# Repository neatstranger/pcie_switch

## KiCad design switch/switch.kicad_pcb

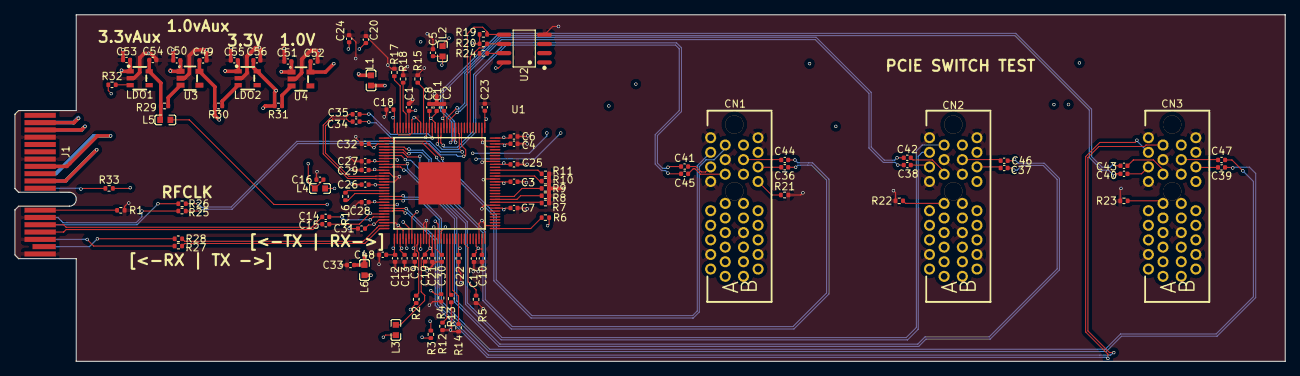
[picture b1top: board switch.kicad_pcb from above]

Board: 6 copper layers, 174.1 x 47.5 mm, 105 parts (0 on the bottom side), 93 nets.

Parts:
C1, C2, C3, C4, C5, C6, C7, C8, C9, C10, C11, C12, C13, C14, C15, C16, C17, C19, C20, C21, C22, C23, C24, C26, C27, C28, C29, C30, C31, C32, C34, C35, C36, C37, C38, C39, C40, C41, C42, C43, C44, C45, C46, C47, C48: 100n; C_0402_1005Metric
C18, C25, C33: 10u; C_0402_1005Metric
C49, C50, C51, C52, C53, C55: 1u; C_0402_1005Metric
C54, C56: 2.2u; C_0402_1005Metric
CN1, CN2, CN3: 3183-10110P1T; CONN-TH_36P-P1.00-V_3183-XXXXXPXT
J1: Bus_PCI_Express_x1; BUS_PCIexpress_x1
L1, L2, L3, L4, L5, L6: MPZ1608D101BTA00; L0603
LDO1, LDO2: TPS70933DBVR; SOT-23-5_L3.0-W1.7-P0.95-LS2.8-BR
R1, R4, R5, R6, R10, R11, R17, R18, R21, R22, R23: 330; R_0402_1005Metric
R2, R3, R19, R20: 5.1k; R_0402_1005Metric
R7, R8, R9, R24: 10k; R_0402_1005Metric
R12, R13, R14: 1k; R_0402_1005Metric
R15: 475; R_0402_1005Metric
R16: 1.42k; R_0402_1005Metric
R25, R26, R27, R28, R29, R30, R31, R32, R33: 0; R_0402_1005Metric
U1: PI7C9X2G404SLBFDEX; LQFP-128_L14.0-W14.0-P0.40-LS16.0-BL-EP5.8
U2: M24C04-WMN6TP; SOIC-8_L4.9-W3.9-P1.27-LS6.0-BL
U3, U4: TLV73310PDBVR; TSOT-23-5_L2.9-W1.6-P0.95-LS2.8-BR

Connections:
/3.3V_PCIE: C50.1, C51.1, C53.2, C55.2, CN1.A5 (TCK), CN1.A6 (TDI), CN1.A8 (TMS), CN1.A9 (+3.3V), CN1.A10 (+3.3V), CN1.B8 (+3.3V), CN1.B9 (nTRST), CN1.B10 (+3.3VAux), CN2.A5 (TCK), CN2.A6 (TDI), CN2.A8 (TMS), CN2.A9 (+3.3V), CN2.A10 (+3.3V), CN2.B8 (+3.3V), CN2.B9 (nTRST), CN2.B10 (+3.3VAux), CN3.A5 (TCK), CN3.A6 (TDI), CN3.A8 (TMS), CN3.A9 (+3.3V), CN3.A10 (+3.3V), CN3.B8 (+3.3V), CN3.B9 (nTRST), CN3.B10 (+3.3VAux), J1.A9 (+3.3V), J1.A10 (+3.3V), J1.B8 (+3.3V), J1.B10 (3.3Vaux), LDO1.1 (IN), LDO2.1 (IN), R32.1, U3.1 (IN), U4.1 (IN)
/+12V_PCIE: CN1.A2 (+12V), CN1.A3 (+12V), CN1.B1 (+12V), CN1.B2 (+12V), CN1.B3 (+12V), CN2.A2 (+12V), CN2.A3 (+12V), CN2.B1 (+12V), CN2.B2 (+12V), CN2.B3 (+12V), CN3.A2 (+12V), CN3.A3 (+12V), CN3.B1 (+12V), CN3.B2 (+12V), CN3.B3 (+12V), J1.A2 (+12V), J1.A3 (+12V), J1.B1 (+12V), J1.B2 (+12V), J1.B3 (+12V)
/PCIE_DOWNSTREAM1/PCIE_TX_N: C44.2, CN1.B15 (PCIE_TX_N)
/PCIE_DOWNSTREAM1/PCIE_TX_P: C36.2, CN1.B14 (PCIE_TX_P)
/PCIE_DOWNSTREAM1/REF_CLK_N: C41.2, CN1.A14 (REF_CLK_N)
/PCIE_DOWNSTREAM1/REF_CLK_P: C45.2, CN1.A13 (REF_CLK_P)
/PCIE_DOWNSTREAM2/PCIE_TX_N: C46.2, CN2.B15 (PCIE_TX_N)
/PCIE_DOWNSTREAM2/PCIE_TX_P: C37.2, CN2.B14 (PCIE_TX_P)
/PCIE_DOWNSTREAM2/REF_CLK_N: C38.2, CN2.A14 (REF_CLK_N)
/PCIE_DOWNSTREAM2/REF_CLK_P: C42.2, CN2.A13 (REF_CLK_P)
/PCIE_DOWNSTREAM3/PCIE_TX_N: C47.2, CN3.B15 (PCIE_TX_N)
/PCIE_DOWNSTREAM3/PCIE_TX_P: C39.2, CN3.B14 (PCIE_TX_P)
/PCIE_DOWNSTREAM3/REF_CLK_N: C40.2, CN3.A14 (REF_CLK_N)
/PCIE_DOWNSTREAM3/REF_CLK_P: C43.2, CN3.A13 (REF_CLK_P)
/PCIE_SWITCH/1.0Vaux: C49.1, L3.2, R30.2, U3.5 (OUT)
/PCIE_SWITCH/3.3V_PCIE: C3.1, C6.1, C9.1, C12.1, C16.1, C18.1, C48.1, L1.2, L2.2, L4.2, R2.1, R3.1, R6.1, R19.1, R20.1, U1.1 (VDDR), U1.8 (VDDR), U1.49 (VDDR), U1.64 (VDDR), U1.96 (VDDR), U2.8 (VCC)
/PCIE_SWITCH/3.3Vaux: C54.2, L5.2, LDO1.5 (OUT), R29.2
/PCIE_SWITCH/+1.0V: C1.2, C4.2, C7.2, C10.2, C13.2, C17.2, C20.2, C22.2, C23.2, C24.2, C25.2, C52.1, L6.2, U1.3 (VDDC), U1.23 (VDDC), U1.29 (VDDC), U1.31 (VDDC), U1.40 (VDDC), U1.55 (VDDC), U1.62 (VDDC), U1.65 (VDDC), U1.91 (VDDC), U4.5 (OUT)
/PCIE_SWITCH/+3.3V: C56.2, L1.1, LDO2.5 (OUT), R31.2
/PCIE_SWITCH/+AVDD: C27.1, C28.1, C29.1, C31.1, C32.1, C33.1, L6.1, U1.99 (AVDD), U1.105 (AVDD), U1.108 (AVDD), U1.119 (AVDD), U1.125 (AVDD)
/PCIE_SWITCH/+AVDDH: C26.1, L4.1, U1.113 (AVDDH)
/PCIE_SWITCH/+CVDDR: C2.1, C5.1, C8.1, C11.1, L2.1, U1.79 (CVDDR), U1.82 (CVDDR), U1.84 (CVDDR)
/PCIE_SWITCH/+VAUX: C30.1, L5.1, U1.15 (VAUX)
/PCIE_SWITCH/+VDDCAUX: C19.1, C21.1, L3.1, U1.13 (VDDCAUX), U1.14 (VDDCAUX)
/PCIE_SWITCH/CLOCKREQ_(0): J1.B12 (CLK_REQ), R1.1
/PCIE_SWITCH/CLOCKREQ_(1): CN1.B12 (nCLK_REQ), R21.1
/PCIE_SWITCH/CLOCKREQ_(2): CN2.A11 (nPERST), R22.1
/PCIE_SWITCH/CLOCKREQ_(3): CN3.A11 (nPERST), R23.1
/PCIE_SWITCH/DWNRST_L(1): CN1.A11 (nPERST), U1.5 (DWNRST_L[1])
/PCIE_SWITCH/DWNRST_L(2): CN2.B12 (nCLK_REQ), U1.6 (DWNRST_L[2])
/PCIE_SWITCH/DWNRST_L(3): CN3.B12 (nCLK_REQ), U1.7 (DWNRST_L[3])
/PCIE_SWITCH/EECLK: R20.2, U1.70 (EECLK), U2.6 (SCL)
/PCIE_SWITCH/EEPD: R19.2, U1.71 (EEPD), U2.5 (SDA)
/PCIE_SWITCH/PCIE_CLK_N: J1.A13 (REFCLK+), R25.1
/PCIE_SWITCH/PCIE_CLK_P: J1.A14 (REFCLK-), R26.1
/PCIE_SWITCH/PCIE_RX_N: C15.1, J1.B15 (PETn0)
/PCIE_SWITCH/PCIE_RX_P: C14.1, J1.B14 (PETp0)
/PCIE_SWITCH/PCIE_TX_N: J1.A17 (PERn0), R28.1
/PCIE_SWITCH/PCIE_TX_P: J1.A16 (PERp0), R27.1
/PCIE_SWITCH/PCIE_nRST: J1.A11 (~PERST), R33.1
/PCIE_SWITCH/PER(0)_N: R28.2, U1.127 (PERN[0])
/PCIE_SWITCH/PER(0)_P: R27.2, U1.128 (PERP[0])
/PCIE_SWITCH/PER(1)_N: CN1.A17 (PCIE_RX_N), U1.98 (PERN[1])
/PCIE_SWITCH/PER(1)_P: CN1.A16 (PCIE_RX_P), U1.97 (PERP[1])
/PCIE_SWITCH/PER(2)_N: CN2.A16 (PCIE_RX_P), U1.103 (PERN[2])
/PCIE_SWITCH/PER(2)_P: CN2.A17 (PCIE_RX_N), U1.102 (PERP[2])
/PCIE_SWITCH/PER(3)_N: CN3.A17 (PCIE_RX_N), U1.121 (PERN[3])
/PCIE_SWITCH/PER(3)_P: CN3.A16 (PCIE_RX_P), U1.122 (PERP[3])
/PCIE_SWITCH/PERST_L: R33.2, U1.10 (PERST_L)
/PCIE_SWITCH/PET(0)_N: C15.2, U1.123 (PETN[0])
/PCIE_SWITCH/PET(0)_P: C14.2, U1.124 (PETP[0])
/PCIE_SWITCH/PET(1)_N: C44.1, U1.101 (PETN[1])
/PCIE_SWITCH/PET(1)_P: C36.1, U1.100 (PETP[1])
/PCIE_SWITCH/PET(2)_N: C46.1, U1.107 (PETN[2])
/PCIE_SWITCH/PET(2)_P: C37.1, U1.106 (PETP[2])
/PCIE_SWITCH/PET(3)_N: C47.1, U1.117 (PETN[3])
/PCIE_SWITCH/PET(3)_P: C39.1, U1.118 (PETP[3])
/PCIE_SWITCH/REFCLK(0)_N: R25.2, U1.73 (REFCLKI_N)
/PCIE_SWITCH/REFCLK(0)_P: R26.2, U1.74 (REFCLKI_P)
/PCIE_SWITCH/REFCLK(1)_N: C41.1, U1.80 (REFCLKO_N[1])
/PCIE_SWITCH/REFCLK(1)_P: C45.1, U1.81 (REFCLKO_P[1])
/PCIE_SWITCH/REFCLK(2)_N: C38.1, U1.77 (REFCLKO_N[2])
/PCIE_SWITCH/REFCLK(2)_P: C42.1, U1.78 (REFCLKO_P[2])
/PCIE_SWITCH/REFCLK(3)_N: C40.1, U1.75 (REFCLKO_N[3])
/PCIE_SWITCH/REFCLK(3)_P: C43.1, U1.76 (REFCLKO_P[3])
/PCIE_SWITCH/REFCLKO0_N: C35.2, U1.111 (REFCLKN)
/PCIE_SWITCH/REFCLKO0_P: C34.2, U1.110 (REFCLKP)
/PCIE_SWITCH/U1-REFLCOK_N: C35.1, U1.83 (REFCLKO_N[0])
/PCIE_SWITCH/U1-REFLCOK_P: C34.1, U1.85 (REFCLKO_P[0])
GND: C1.1, C2.2, C3.2, C4.1, C5.2, C6.2, C7.1, C8.2, C9.2, C10.1, C11.2, C12.2, C13.1, C16.2, C17.1, C18.2, C19.2, C20.1, C21.2, C22.1, C23.1, C24.1, C25.1, C26.2, C27.2, C28.2, C29.2, C30.2, C31.2, C32.2, C33.2, C48.2, C49.2, C50.2, C51.2, C52.2, C53.1, C54.1, C55.1, C56.1, CN1.A4 (GND), CN1.A12 (GND), CN1.A15 (GND), CN1.A18 (GND), CN1.B4 (GND), CN1.B7 (GND), CN1.B13 (GND), CN1.B16 (GND), CN1.B18 (GND), CN2.A4 (GND), CN2.A12 (GND), CN2.A15 (GND), CN2.A18 (GND), CN2.B4 (GND), CN2.B7 (GND), CN2.B13 (GND), CN2.B16 (GND), CN2.B18 (GND), CN3.A4 (GND), CN3.A12 (GND), CN3.A15 (GND), CN3.A18 (GND), CN3.B4 (GND), CN3.B7 (GND), CN3.B13 (GND), CN3.B16 (GND), CN3.B18 (GND), J1.A4 (GND), J1.A12 (GND), J1.A15 (GND), J1.A18 (GND), J1.B4 (GND), J1.B7 (GND), J1.B13 (GND), J1.B16 (GND), J1.B18 (GND), LDO1.2 (GND), LDO2.2 (GND), R1.2, R4.1, R5.1, R7.2, R8.2, R9.2, R10.1, R11.1, R12.1, R13.1, R14.1, R15.2, R17.2, R18.2, R21.2, R22.2, R23.2, R24.1, U1.2 (VSS), U1.4 (VSS), U1.11 (VSS), U1.12 (VSS), U1.30 (VSS), U1.32 (VSS), U1.34 (VSS), U1.41 (VSS), U1.50 (VSS), U1.56 (VSS), U1.61 (VSS), U1.63 (VSS), U1.66 (VSS), U1.87 (VSS), U1.90 (VSS), U1.95 (VSS), U1.104 (VSS), U1.109 (CGND), U1.112 (CGND), U1.120 (VSS), U1.126 (VSS), U1.129 (EP), U2.4 (VSS), U3.2 (GND), U4.2 (GND)
unnamed: LDO1.3 (EN), R32.2
unnamed: LDO2.3 (EN), R30.1
unnamed: R7.1, U1.42 (GPIO[5])
unnamed: R8.1, U1.43 (GPIO[6])
unnamed: R9.1, U1.44 (GPIO[7])
unnamed: R15.1, U1.86 (IREF)
unnamed: R11.2, U1.53 (PL_512B)
unnamed: R12.2, U1.19 (PRSNT[1])
unnamed: R13.2, U1.20 (PRSNT[2])
unnamed: R14.2, U1.21 (PRSNT[3])
unnamed: R16.1, U1.116 (REXT)
unnamed: R16.2, U1.115 (REXT_GND)
unnamed: R6.2, U1.33 (SLOTCLK)
unnamed: R2.2, U1.9 (TEST1)
unnamed: R3.2, U1.16 (TEST2)
unnamed: R4.2, U1.17 (TEST3)
unnamed: R5.2, U1.25 (TEST5)
unnamed: R10.2, U1.51 (TEST6)
unnamed: R18.1, U1.92 (TMS)
unnamed: R17.1, U1.94 (TRST_L)
unnamed: R24.2, U2.7 (~WC)
unnamed: R29.1, U3.3 (EN)
unnamed: R31.1, U4.3 (EN)

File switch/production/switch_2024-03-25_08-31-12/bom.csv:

Designator,Footprint,Quantity,Value,LCSC Part #
"C1, C10, C11, C12, C13, C14, C15, C16, C17, C19, C2, C20, C21, C22, C23, C24, C26, C27, C28, C29, C3, C30, C31, C32, C34, C35, C36, C37, C38, C39, C4, C40, C41, C42, C43, C44, C45, C46, C47, C48, C5, C6, C7, C8, C9",0402,45,100n,C309458
"C18, C25, C33",0402,3,10u,C315248
"C49, C50, C51, C52, C53, C55",0402,6,1u,
"C54, C56",0402,2,2.2u,
"CN1, CN2, CN3",CONN-TH_36P-P1.00-V_3183-XXXXXPXT,3,3183-10110P1T,C404109
J1,BUS_PCIexpress_x1,1,Bus_PCI_Express_x1,
"L1, L2, L3, L4, L5, L6",L0603,6,MPZ1608D101BTA00,C87554
"LDO1, LDO2",SOT-23-5_L3.0-W1.7-P0.95-LS2.8-BR,2,TPS70933DBVR,C89347
"R1, R21, R22, R23",0402,4,330,
"R10, R11, R17, R18, R4, R5, R6",0402,7,330,C25104
"R12, R13, R14",0402,3,1k,C11702
R15,0402,1,475,
R16,0402,1,1.42k,C25744
"R19, R2, R20, R3",0402,4,5.1k,C25905
"R24, R7, R8, R9",0402,4,10k,C25744
"R25, R26, R27, R28, R29, R30, R31, R32, R33",0402,9,0,
U1,LQFP-128_L14.0-W14.0-P0.40-LS16.0-BL-EP5.8,1,PI7C9X2G404SLBFDEX,C500767
U2,SOIC-8_L4.9-W3.9-P1.27-LS6.0-BL,1,M24C04-WMN6TP,C118280
"U3, U4",TSOT-23-5_L2.9-W1.6-P0.95-LS2.8-BR,2,TLV73310PDBVR,C83352

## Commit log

2024-03-22 Added Basic Stuff.
2024-03-22 WOrking.
2024-03-22 Working on power supplies.
2024-03-22 Working on PSU's
2024-03-22 Finished with Schematic.
2024-03-22 Working on layout.
2024-03-22 Layout is finished.
2024-03-22 CLoseout
2024-03-25 Finished with routing.
2024-03-25 Added Production files.
